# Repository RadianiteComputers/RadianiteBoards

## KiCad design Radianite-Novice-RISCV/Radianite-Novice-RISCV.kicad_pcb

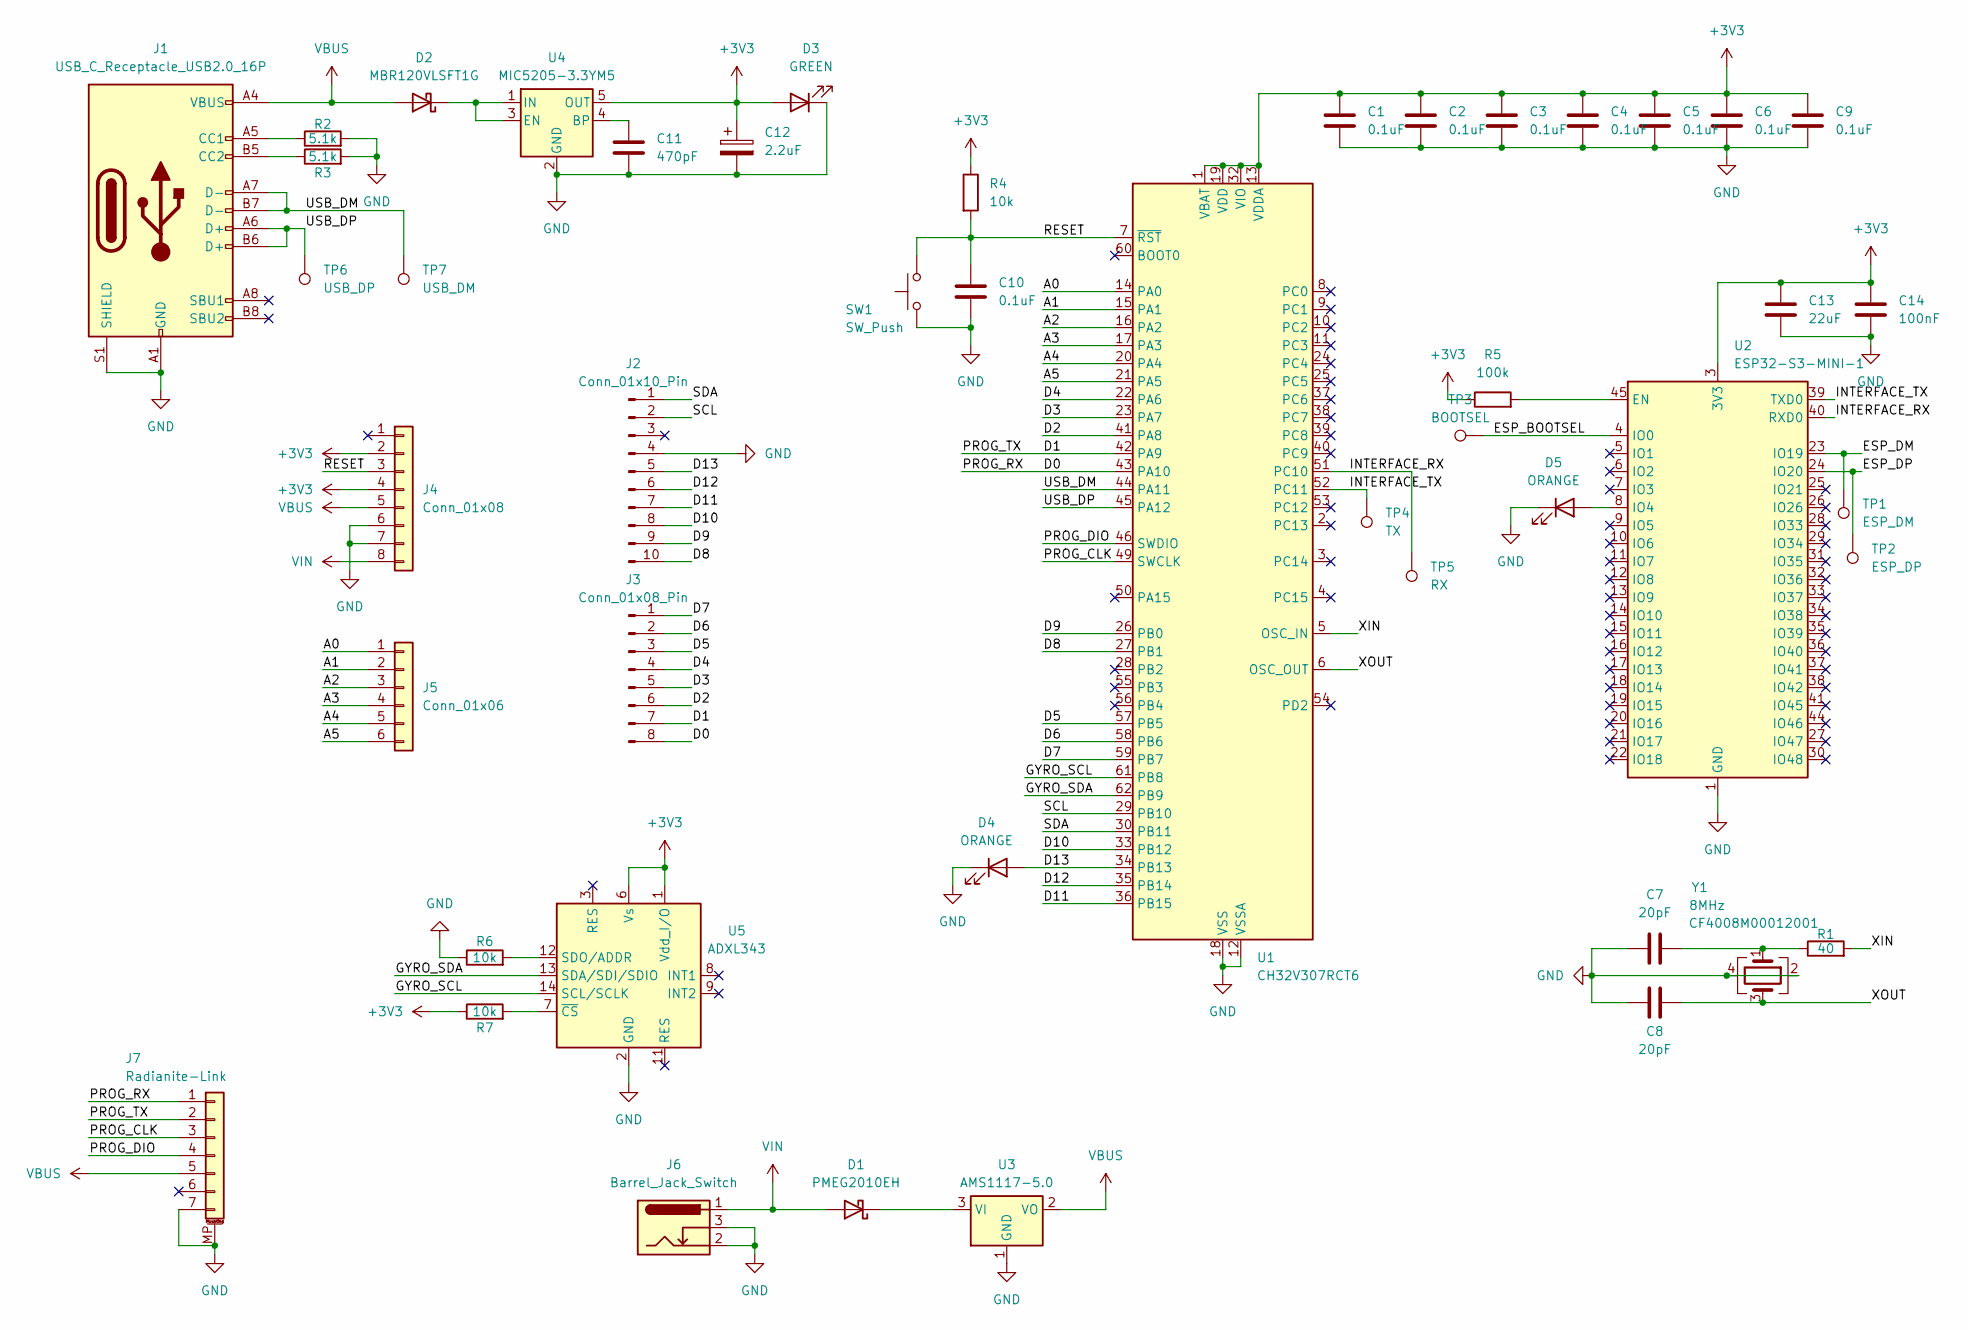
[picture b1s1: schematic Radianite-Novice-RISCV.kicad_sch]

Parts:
C1, C2, C3, C4, C5, C6, C9, C10: 0.1uF; C_0402_1005Metric
C7, C8: 20pF; C_0402_1005Metric
C11: 470pF; C_0402_1005Metric
C12: 2.2uF; CP_EIA-1608-08_AVX-J
C13: 22uF; C_0402_1005Metric
C14: 100nF; C_0402_1005Metric
D1: PMEG2010EH; D_SOD-123F
D2: MBR120VLSFT1G; D_SOD-123F
D3: GREEN; LED_0402_1005Metric
D4, D5: ORANGE; LED_0402_1005Metric
J1: USB_C_Receptacle_USB2.0_16P; USB_C_Receptacle_GCT_USB4105-xx-A_16P_TopMnt_Horizontal
J2: Conn_01x10_Pin; PinSocket_1x10_P2.54mm_Vertical
J3: Conn_01x08_Pin; PinSocket_1x08_P2.54mm_Vertical
J4: Conn_01x08; PinSocket_1x08_P2.54mm_Vertical
J5: Conn_01x06; PinSocket_1x06_P2.54mm_Vertical
J6: Barrel_Jack_Switch; BarrelJack_Horizontal
J7: Radianite-Link; JST_SH_SM07B-SRSS-TB_1x07-1MP_P1.00mm_Horizontal
R1: 40; R_0402_1005Metric
R2, R3: 5.1k; R_0402_1005Metric
R4, R6, R7: 10k; R_0402_1005Metric
R5: 100k; R_0402_1005Metric
SW1: SW_Push; SW_SPST_Omron_B3FS-100xP
TP1: ESP_DM; TestPoint_Pad_D1.0mm
TP2: ESP_DP; TestPoint_Pad_D1.0mm
TP3: BOOTSEL; TestPoint_Pad_D1.0mm
TP4: TX; TestPoint_Pad_D1.0mm
TP5: RX; TestPoint_Pad_D1.0mm
TP6: USB_DP; TestPoint_Pad_D1.0mm
TP7: USB_DM; TestPoint_Pad_D1.0mm
U1: CH32V307RCT6; LQFP-64_10x10mm_P0.5mm
U2: ESP32-S3-MINI-1; ESP32-S2-MINI-1
U3: AMS1117-5.0; SOT-223-3_TabPin2
U4: MIC5205-3.3YM5; SOT-23-5
U5: ADXL343; LGA-14_3x5mm_P0.8mm_LayoutBorder1x6y
Y1: 8MHz; Crystal_SMD_3225-4Pin_3.2x2.5mm

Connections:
+3V3: C1.1, C2.1, C3.1, C4.1, C5.1, C6.1, C9.1, C12.1, C13.1, C14.1, D3.2 (A), J4.2, J4.4, R4.1, R5.1, R7.1, U1.1 (VBAT), U1.13 (VDDA), U1.19 (VDD), U1.32 (VIO), U1.48 (VDD), U1.64 (VIO), U2.3 (3V3), U4.5 (OUT), U5.1 (Vdd_I/O), U5.6 (Vs)
/A0: J5.1, U1.14 (PA0)
/A1: J5.2, U1.15 (PA1)
/A2: J5.3, U1.16 (PA2)
/A3: J5.4, U1.17 (PA3)
/A4: J5.5, U1.20 (PA4)
/A5: J5.6, U1.21 (PA5)
/D0: J3.8, J7.1, U1.43 (PA10)
/D1: J3.7, J7.2, U1.42 (PA9)
/D2: J3.6, U1.41 (PA8)
/D3: J3.5, U1.23 (PA7)
/D4: J3.4, U1.22 (PA6)
/D5: J3.3, U1.57 (PB5)
/D6: J3.2, U1.58 (PB6)
/D7: J3.1, U1.59 (PB7)
/D8: J2.10, U1.27 (PB1)
/D9: J2.9, U1.26 (PB0)
/D10: J2.8, U1.33 (PB12)
/D11: J2.7, U1.36 (PB15)
/D12: J2.6, U1.35 (PB14)
/D13: D4.2 (A), J2.5, U1.34 (PB13)
/ESP_BOOTSEL: TP3.1, U2.4 (IO0)
/ESP_DM: TP1.1, U2.23 (IO19)
/ESP_DP: TP2.1, U2.24 (IO20)
/GYRO_SCL: U1.61 (PB8), U5.14 (SCL/SCLK)
/GYRO_SDA: U1.62 (PB9), U5.13 (SDA/SDI/SDIO)
/INTERFACE_RX: TP5.1, U1.51 (PC10), U2.40 (RXD0)
/INTERFACE_TX: TP4.1, U1.52 (PC11), U2.39 (TXD0)
/PROG_CLK: J7.3, U1.49 (SWCLK)
/PROG_DIO: J7.4, U1.46 (SWDIO)
/RESET: C10.1, J4.3, R4.2, SW1.2, U1.7 (~RST)
/SCL: J2.2, U1.29 (PB10)
/SDA: J2.1, U1.30 (PB11)
/USB_DM: J1.A7 (D-), J1.B7 (D-), TP7.1, U1.44 (PA11)
/USB_DP: J1.A6 (D+), J1.B6 (D+), TP6.1, U1.45 (PA12)
/XIN: R1.2, U1.5 (OSC_IN)
/XOUT: C8.1, U1.6 (OSC_OUT), Y1.3
GND: C1.2, C2.2, C3.2, C4.2, C5.2, C6.2, C7.1, C8.2, C9.2, C10.2, C11.2, C12.2, C13.2, C14.2, D3.1 (K), D4.1 (K), D5.1 (K), J1.A1 (GND), J1.A12 (GND), J1.B1 (GND), J1.B12 (GND), J1.S1 (SHIELD), J2.4, J4.6, J4.7, J6.2, J6.3, J7.7, J7.MP (MountPin), R2.2, R3.2, R6.1, SW1.1, U1.12 (VSSA), U1.18 (VSS), U1.31 (VSS), U1.47 (VSS), U1.63 (VSS), U2.1 (GND), U2.2 (GND), U2.42 (GND), U2.43 (GND), U2.46 (GND), U2.47 (GND), U2.48 (GND), U2.49 (GND), U2.50 (GND), U2.51 (GND), U2.52 (GND), U2.53 (GND), U2.54 (GND), U2.55 (GND), U2.56 (GND), U2.57 (GND), U2.58 (GND), U2.59 (GND), U2.60 (GND), U2.61 (GND), U2.62 (GND), U2.63 (GND), U2.64 (GND), U2.65 (GND), U3.1 (GND), U4.2 (GND), U5.2 (GND), U5.4 (GND), U5.5 (GND), Y1.2, Y1.4
unnamed: C7.2, R1.1, Y1.1
unnamed: D1.1 (K), U3.3 (VI)
unnamed: D2.1 (K), U4.1 (IN), U4.3 (EN)
unnamed: D5.2 (A), U2.8 (IO4)
unnamed: J1.A5 (CC1), R2.1
unnamed: J1.B5 (CC2), R3.1
unnamed: R5.2, U2.45 (EN)
unnamed: C11.1, U4.4 (BP)
unnamed: R6.2, U5.12 (SDO/ADDR)
unnamed: R7.2, U5.7 (~CS)
VBUS: D2.2 (A), J1.A4 (VBUS), J1.A9 (VBUS), J1.B4 (VBUS), J1.B9 (VBUS), J4.5, J7.5, U3.2 (VO)
VIN: D1.2 (A), J4.8, J6.1

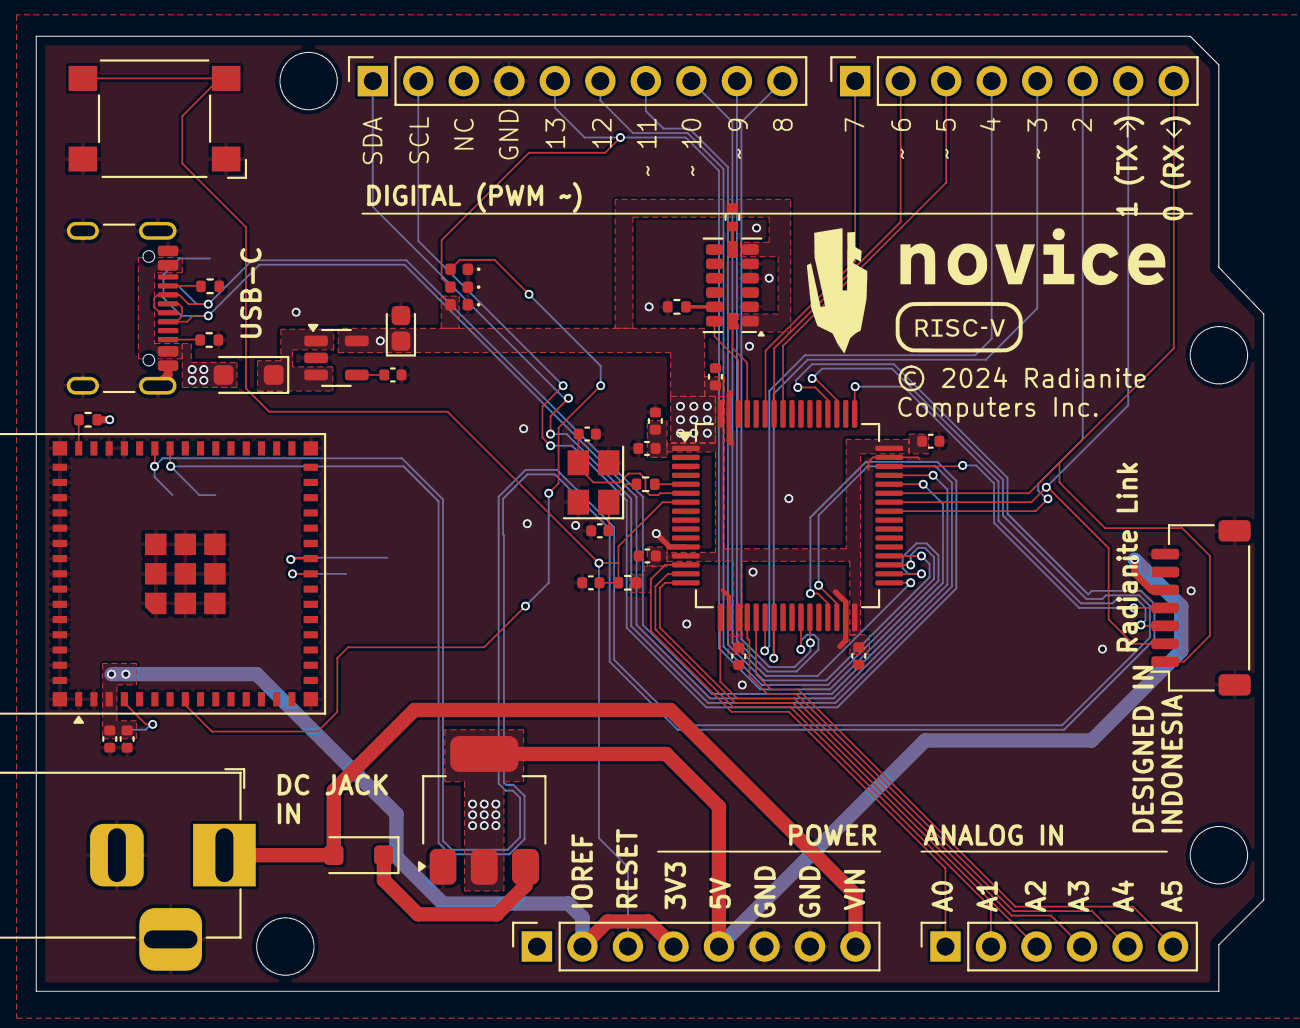
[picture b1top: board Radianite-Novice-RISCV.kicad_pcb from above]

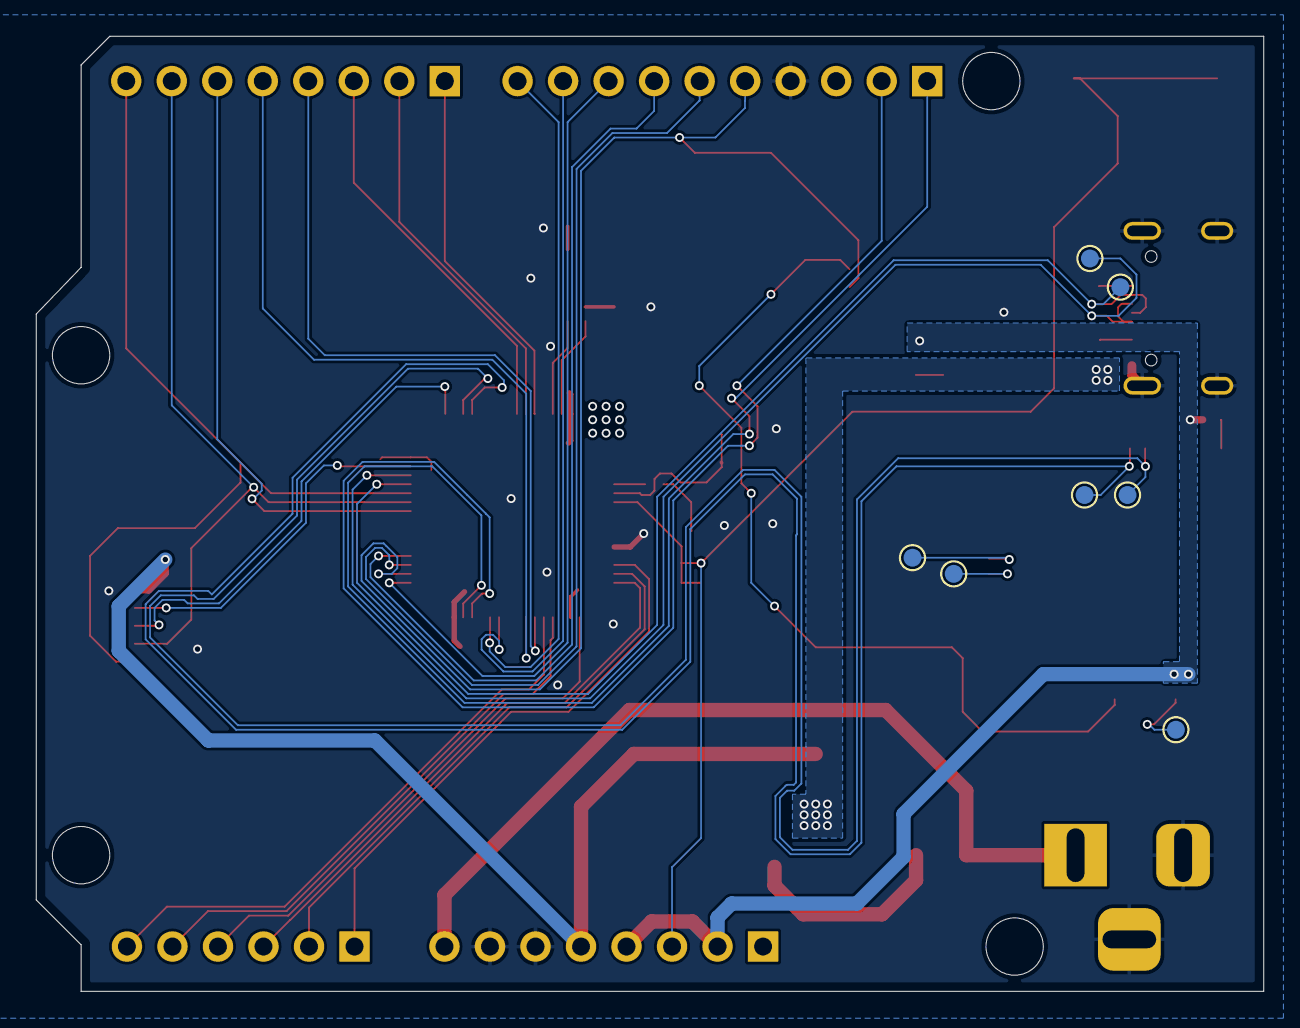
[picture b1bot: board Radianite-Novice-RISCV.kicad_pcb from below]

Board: 2 copper layers, 68.5 x 53.3 mm, 47 parts (7 on the bottom side), 50 nets.

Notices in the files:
Radianite-Novice-RISCV/Radianite-Novice-RISCV.kicad_pcb:
©️ 2024 Radianite
